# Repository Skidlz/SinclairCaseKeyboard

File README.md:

# Sinclair Case & Keyboard
A new case and keyboard for the Timex Sinclair 1000 computer

Includes design files for:
* acrylic case
* keyboard pcb
* keyboard plate
* keyboard flat flex cable

### Case
The case was designed using Inkscape and cut at Ponoko using their 3.00mm "Black Matte Acrylic"

The text was painted using Tamiya "TS-27 Matt White" and Testors "1250T Flat Red"

### PCBs
The boards were designed in Eagle CAD and fabbed at JLCPCB

The plate is 1.2mm black FR-4 (select "Remove Mark")

The flex cable is 0.11mm with a 0.20mm polyimide stiffener

### Keyboard
The switches are blue Redragon low profile

The keycaps were taken from a Redragon K603 keyboard

The key labels come from [4keyboard.com](https://www.4keyboard.com/commodore-keyboard-stickers/647-3006-sinclair-zx-spectrum-non-transparent-keyboard-stickers.html)

# Modifications
The motherboard has to be modified to fit the new case. This means removing the RF modulator, voltage regulator, and heatsink.

I chose to replace the modulator with a composite video board from [Ginger Electronic](https://www.ginger-electronic.com/en/retro-computer/21-zx8-ccb-video-mod-for-sinclair-zx80-and-zx81.html).

The regulator was replaced with a generic buck converter that fits in the TO-220 footprint.

# Images

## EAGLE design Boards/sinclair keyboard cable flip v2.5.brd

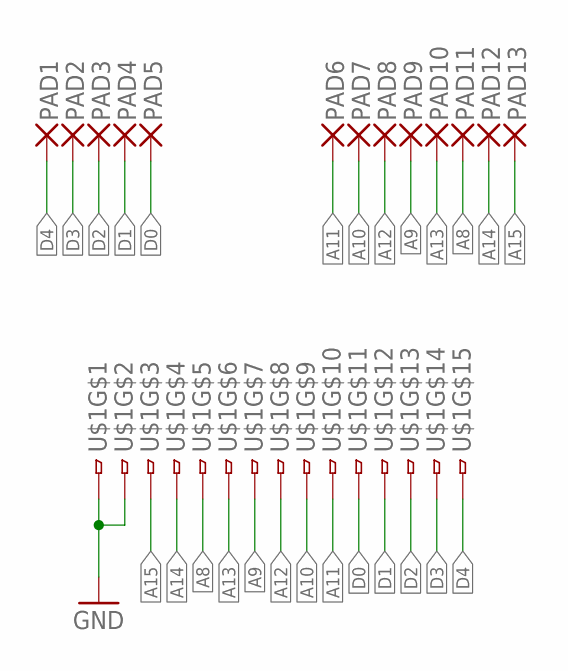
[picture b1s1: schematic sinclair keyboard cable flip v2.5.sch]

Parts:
PAD1, PAD2, PAD3, PAD4, PAD5, PAD6, PAD7, PAD8, PAD9, PAD10, PAD11, PAD12, PAD13: SMD230MIL; SMD1,27-762
U$1: FH12-15S-1SHFFC; FFC-15

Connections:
A8: PAD11.1, U$1.5
A9: PAD9.1, U$1.7
A10: PAD7.1, U$1.9
A11: PAD6.1, U$1.10
A12: PAD8.1, U$1.8
A13: PAD10.1, U$1.6
A14: PAD12.1, U$1.4
A15: PAD13.1, U$1.3
D0: PAD5.1, U$1.11
D1: PAD4.1, U$1.12
D2: PAD3.1, U$1.13
D3: PAD2.1, U$1.14
D4: PAD1.1, U$1.15
GND: U$1.1, U$1.2

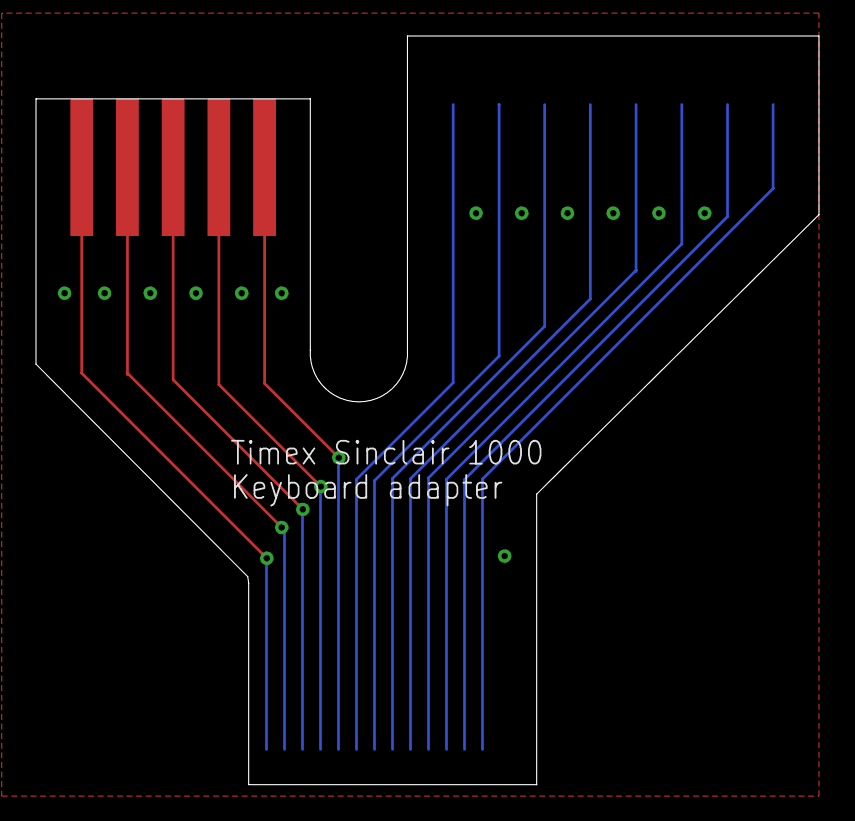
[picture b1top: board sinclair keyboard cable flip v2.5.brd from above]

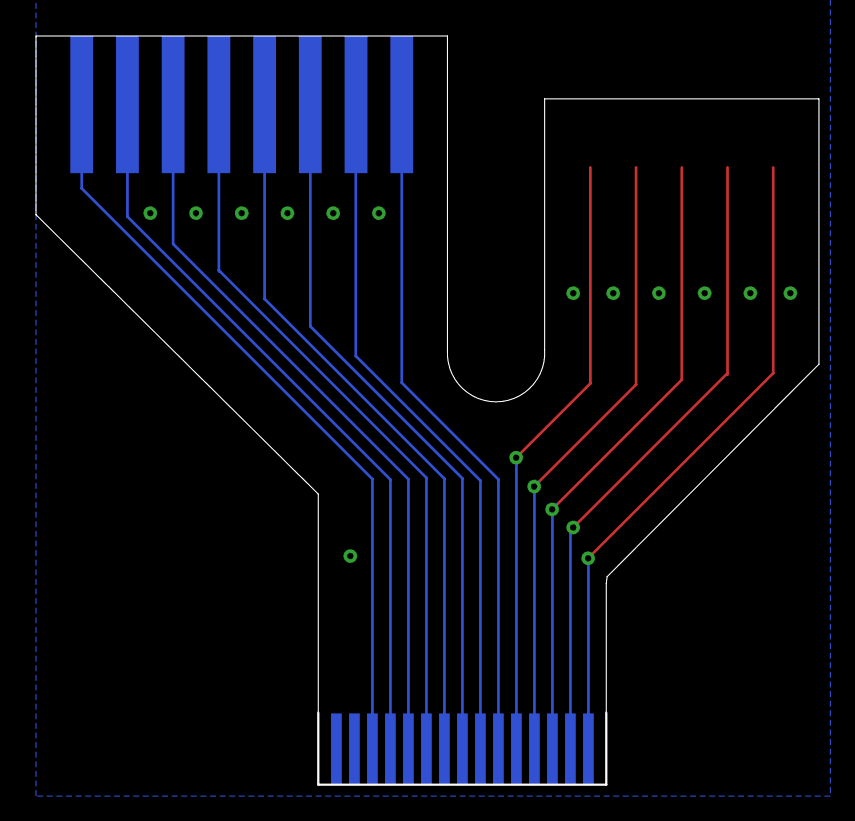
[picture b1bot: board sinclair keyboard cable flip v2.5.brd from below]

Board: 2 copper layers, 43.5 x 41.6 mm, 14 parts (9 on the bottom side), 14 nets.

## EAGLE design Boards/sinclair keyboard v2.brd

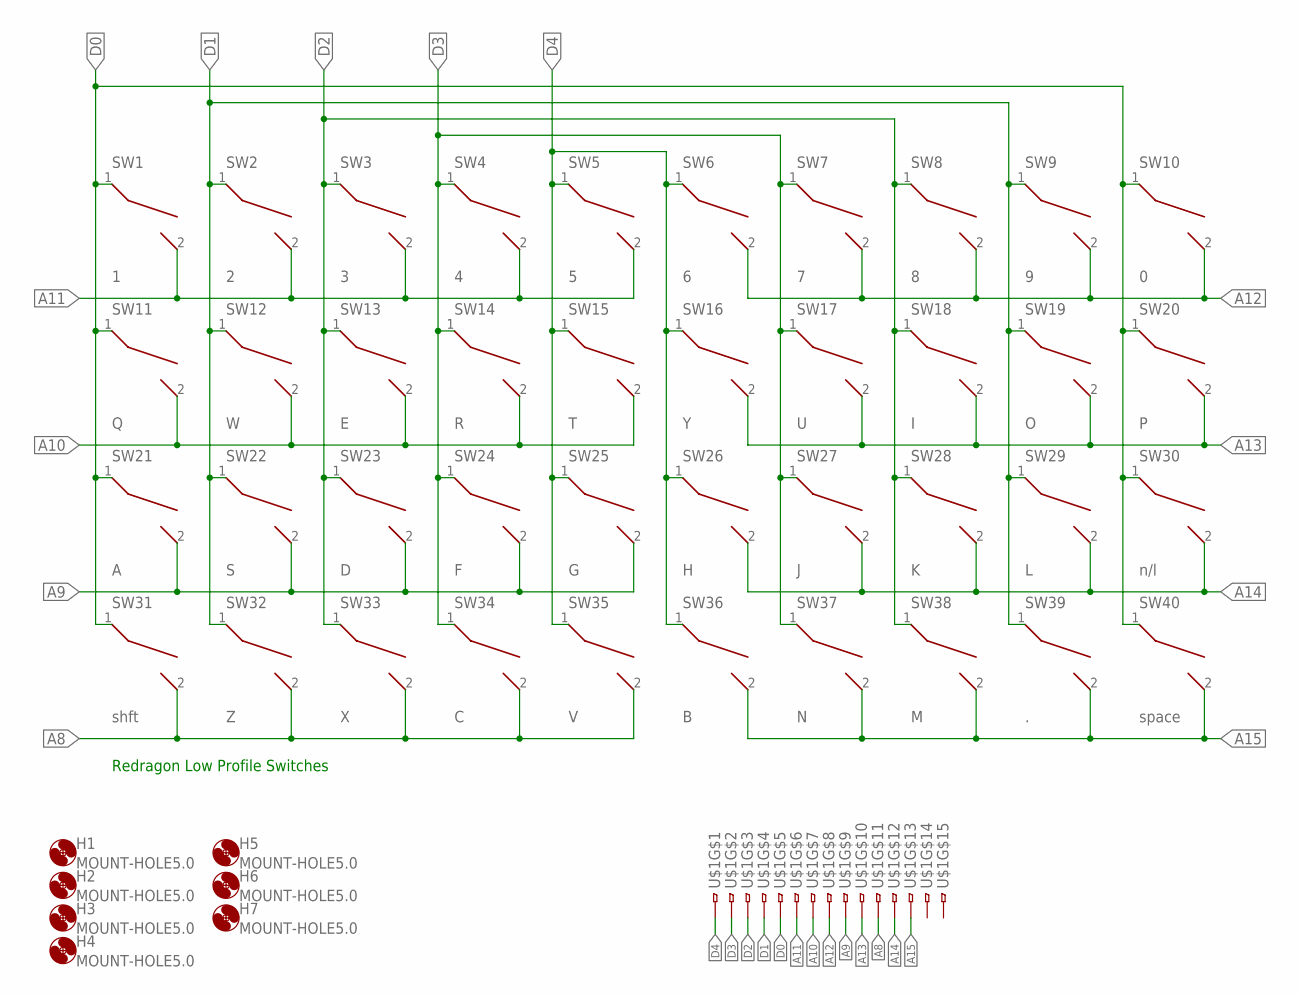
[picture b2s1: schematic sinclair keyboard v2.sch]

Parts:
H1, H2, H3, H4, H5, H6, H7: MOUNT-HOLE5.0; 5,0
SW1: 1; REDRAGON_LOWPROFILE
SW2: 2; REDRAGON_LOWPROFILE
SW3: 3; REDRAGON_LOWPROFILE
SW4: 4; REDRAGON_LOWPROFILE
SW5: 5; REDRAGON_LOWPROFILE
SW6: 6; REDRAGON_LOWPROFILE
SW7: 7; REDRAGON_LOWPROFILE
SW8: 8; REDRAGON_LOWPROFILE
SW9: 9; REDRAGON_LOWPROFILE
SW10: 0; REDRAGON_LOWPROFILE
SW11: Q; REDRAGON_LOWPROFILE
SW12: W; REDRAGON_LOWPROFILE
SW13: E; REDRAGON_LOWPROFILE
SW14: R; REDRAGON_LOWPROFILE
SW15: T; REDRAGON_LOWPROFILE
SW16: Y; REDRAGON_LOWPROFILE
SW17: U; REDRAGON_LOWPROFILE
SW18: I; REDRAGON_LOWPROFILE
SW19: O; REDRAGON_LOWPROFILE
SW20: P; REDRAGON_LOWPROFILE
SW21: A; REDRAGON_LOWPROFILE
SW22: S; REDRAGON_LOWPROFILE
SW23: D; REDRAGON_LOWPROFILE
SW24: F; REDRAGON_LOWPROFILE
SW25: G; REDRAGON_LOWPROFILE
SW26: H; REDRAGON_LOWPROFILE
SW27: J; REDRAGON_LOWPROFILE
SW28: K; REDRAGON_LOWPROFILE
SW29: L; REDRAGON_LOWPROFILE
SW30: n/l; REDRAGON_LOWPROFILE
SW31: shft; REDRAGON_LOWPROFILE
SW32: Z; REDRAGON_LOWPROFILE
SW33: X; REDRAGON_LOWPROFILE
SW34: C; REDRAGON_LOWPROFILE
SW35: V; REDRAGON_LOWPROFILE
SW36: B; REDRAGON_LOWPROFILE
SW37: N; REDRAGON_LOWPROFILE
SW38: M; REDRAGON_LOWPROFILE
SW39: .; REDRAGON_LOWPROFILE
SW40: space; REDRAGON_LOWPROFILE
U$1: FH12-15S-1SH

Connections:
A8: SW31.2, SW32.2, SW33.2, SW34.2, SW35.2, U$1.11
A9: SW21.2, SW22.2, SW23.2, SW24.2, SW25.2, U$1.9
A10: SW11.2, SW12.2, SW13.2, SW14.2, SW15.2, U$1.7
A11: SW1.2, SW2.2, SW3.2, SW4.2, SW5.2, U$1.6
A12: SW6.2, SW7.2, SW8.2, SW9.2, SW10.2, U$1.8
A13: SW16.2, SW17.2, SW18.2, SW19.2, SW20.2, U$1.10
A14: SW26.2, SW27.2, SW28.2, SW29.2, SW30.2, U$1.12
A15: SW36.2, SW37.2, SW38.2, SW39.2, SW40.2, U$1.13
D0: SW1.1, SW10.1, SW11.1, SW20.1, SW21.1, SW30.1, SW31.1, SW40.1, U$1.5
D1: SW2.1, SW9.1, SW12.1, SW19.1, SW22.1, SW29.1, SW32.1, SW39.1, U$1.4
D2: SW3.1, SW8.1, SW13.1, SW18.1, SW23.1, SW28.1, SW33.1, SW38.1, U$1.3
D3: SW4.1, SW7.1, SW14.1, SW17.1, SW24.1, SW27.1, SW34.1, SW37.1, U$1.2
D4: SW5.1, SW6.1, SW15.1, SW16.1, SW25.1, SW26.1, SW35.1, SW36.1, U$1.1

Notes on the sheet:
Redragon Low Profile Switches

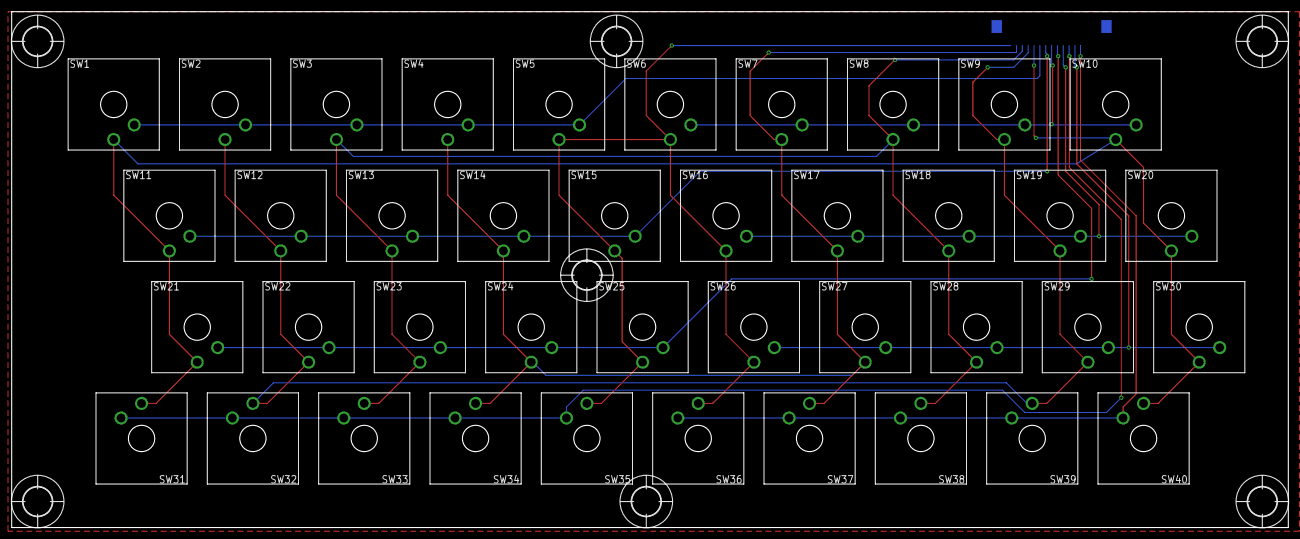
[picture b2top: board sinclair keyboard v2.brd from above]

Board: 2 copper layers, 218.4 x 88.3 mm, 48 parts (1 on the bottom side), 13 nets.

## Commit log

2025-01-19 Init
